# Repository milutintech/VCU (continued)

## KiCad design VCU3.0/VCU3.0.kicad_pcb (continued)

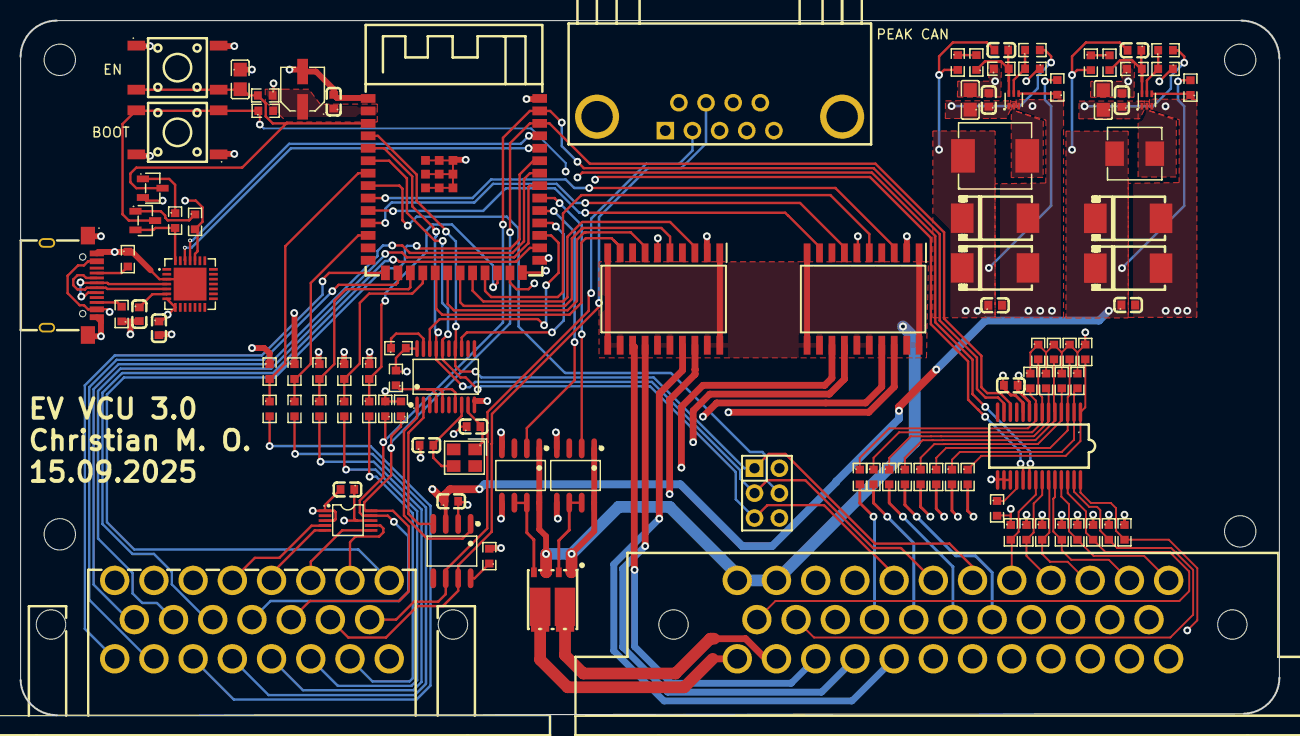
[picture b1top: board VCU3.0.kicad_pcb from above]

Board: 4 copper layers, 128.4 x 70.8 mm, 109 parts (0 on the bottom side), 115 nets.

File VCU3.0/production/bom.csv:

Designator,Footprint,Quantity,Value,LCSC Part #
"C201, C207",C0805,2,10uF,C1713
"C202, C206, C208, C212, C303, C304, C305, C401, C404, C601",C0603,10,100nF,C14663
"C203, C209",C0603,2,10pF,C325468
"C204, C205, C210, C211",CAP-SMD_L7.3-W4.3-L-FD,4,22uF,C347543
C301,C0805,1,1uF,C28323
C302,CAP-SMD_BD4.0-L4.3-W4.3-LS5.1-FD,1,22uF,C131114
"C402, C403",C0603,2,22pF,C105620
H302,HDR-TH_6P-P2.54-V-M-R2-C3-S2.54-1,1,2x3,C65114
"IC602, IC603",SOIC127P1030X265-20N,2,BTS716GB,
L201,IND-SMD_L7.3-W6.6,1,3.3uH,C351116
"R201, R206, R207, R209, R301, R304, R305, R306, R401",R0603,9,10k,C98220
"R202, R208, R211, R402",R0603,4,210k,C217875
R203,R0603,1,43k,C137719
"R204, R210, R212",R0603,3,30k,C113302
"R205, R302, R303",R0603,3,2.2k,C227479
"R307, R308",R0603,2,5.1k,C186203
R403,R0603,1,10,C403411
"R404, R405, R406, R407, R408, R601, R603, R605, R607, R609, R611, R613, R615, R617, R618, R619, R620, R621, R622, R623, R624, R625",R0603,22,7.5k,C328377
"R411, R412, R413, R414, R415, R602, R604, R606, R608, R610, R612, R614, R616",R0603,13,2.7k,C3017728
"U201, U202",SOT-563-6_L1.6-W1.2-P0.5-LS1.6-BR,2,TPS564257DRLR,C19272233
U203,IND-SMD_L5.4-W5.2,1,SLO0530H4R7MTT,C325964
U301,WIRELM-SMD_ESP32-S3-WROOM-1,1,ESP32-S3-WROOM-1(N8R2),C2913204
"U302, U304",SOT-23-3_L2.9-W1.3-P1.90-LS2.4-BR,2,BC817,C549442
U303,QFN-28_L5.0-W5.0-P0.50-TL-EP3.3,1,CP2102N-A02-GQFN28R,C964632
U305,USB-C-SMD_YTC-TC16S-24,1,YTC-TC16S-24,C2927291
U401,SOIC-8_L4.9-W3.9-P1.27-LS6.0-BL,1,MCP2551-I/SN,C7376
U402,TSSOP-20_L6.5-W4.4-P0.65-LS6.4-BL,1,MCP2515-I/ST,C15193
U403,VSSOP-10_L3.0-W3.0-P0.50-LS4.9-BL,1,ADS1015IDGST,C701606
U507,DB9-TH_D-SUB-DR-9PCM-CB,1,D-SUB-DR-9PCM-CB,C19077337
"U601, U602",SOIC-8_L4.9-W3.9-P1.27-LS6.0-BL,2,TC4429COA,C636901
U603,PDFN-8_L5.9-W5.2-P1.27-LS6.2-BL-1,1,VBQA4317,C7541192
U604,SSOP-28_L10.2-W5.3-P0.65-LS7.8-BL,1,MCP23017-E/SS,C506653
U605,CONN-TH_776163-1,1,776163-1,C412117
U606,CONN-TH_776087-1,1,776087-1,C378893
"U607, U608",SW-SMD_4P-L6.0-W6.0-P4.50-LS9.0-H7.3,2,HX-6X6X7_3-TP_FT_SQUARE_BUTTON,C49234152
X401,CRYSTAL-SMD_4P-L3.2-W2.5-BL,1,K3A160002010,C368736

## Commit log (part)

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2024-12-05 Comitted the bs
2024-12-05 dang
2024-12-05 legacy
2024-12-05 Create Workflow
2024-12-05 bs is gone
2024-12-05 webpage
2024-12-05 new version num
2024-12-18 Update can_manager.cpp
    back to normal
2024-12-21 added fucking pins
2024-12-21 new changes
2024-12-21 mimimi
2024-12-29 tests shold be next
2024-12-30 running (legacy only)
2024-12-30 it was working short
2025-02-14 cahnged gitnore
2025-02-15 New opd logic
2025-03-03 compileing
2025-03-05 updated to fit new battery config
2025-03-05 first drive
2025-03-06 Applied torque limits
2025-03-06 drive mode set correctly
2025-03-06 Maybe Maybe nananna
2025-03-06 added safety for charging
2025-03-06 did many changes
2025-03-06 charger getting further but bno precharge
2025-03-06 working
2025-03-06 charging no interrupt handling jet
2025-03-06 charging working mint
2025-03-06 working on regen still osc bur chareg fixxed
2025-03-07 tafügg
2025-03-09 regen mostly working
2025-03-10 okay
2025-03-11 nice
2025-03-11 added config
2025-03-11 good
2025-03-11 aded quit a fev optimazitions
2025-03-11 nice going dick
2025-03-11 okay okay
2025-03-11 kinda working
2025-03-11 nonono
2025-04-27 läuft
2025-05-02 oumps
2025-05-02 current update
2025-05-05 Screen implemented esp now
2025-05-05 added infoscreen
2025-05-08 simple regen
2025-05-08 regen is better
2025-05-09 adapted for papap
2025-05-09 HHHHHHH
2025-05-09 tests
2025-05-09 bit rugth
2025-05-09 worki
2025-05-12 finaly
2025-05-22 mimi
2025-08-20 updated for hall pedal
2025-08-25 Added reco mode
2025-09-14 got it driving
2025-09-14 reduced REQU
2025-09-15 fuuuuuck
2025-09-15 new driving mode
2025-09-15 och man
2025-09-15 removed unneccesarry debug shit
2025-09-15 back to basics
2025-09-16 defaults changed
2025-09-16 new defaults
2025-09-27 added ui
2025-10-17 Added VCU 3.09
2025-10-24 maybe now
2026-05-29 i guess i forgur to commit
2026-05-29 removed unused files
2026-06-04 fixed one fet circuit
